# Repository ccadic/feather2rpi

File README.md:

# feather2rpi
Feather2RPIShield Adaptor
Use RPI shield / RPI display with a feather board

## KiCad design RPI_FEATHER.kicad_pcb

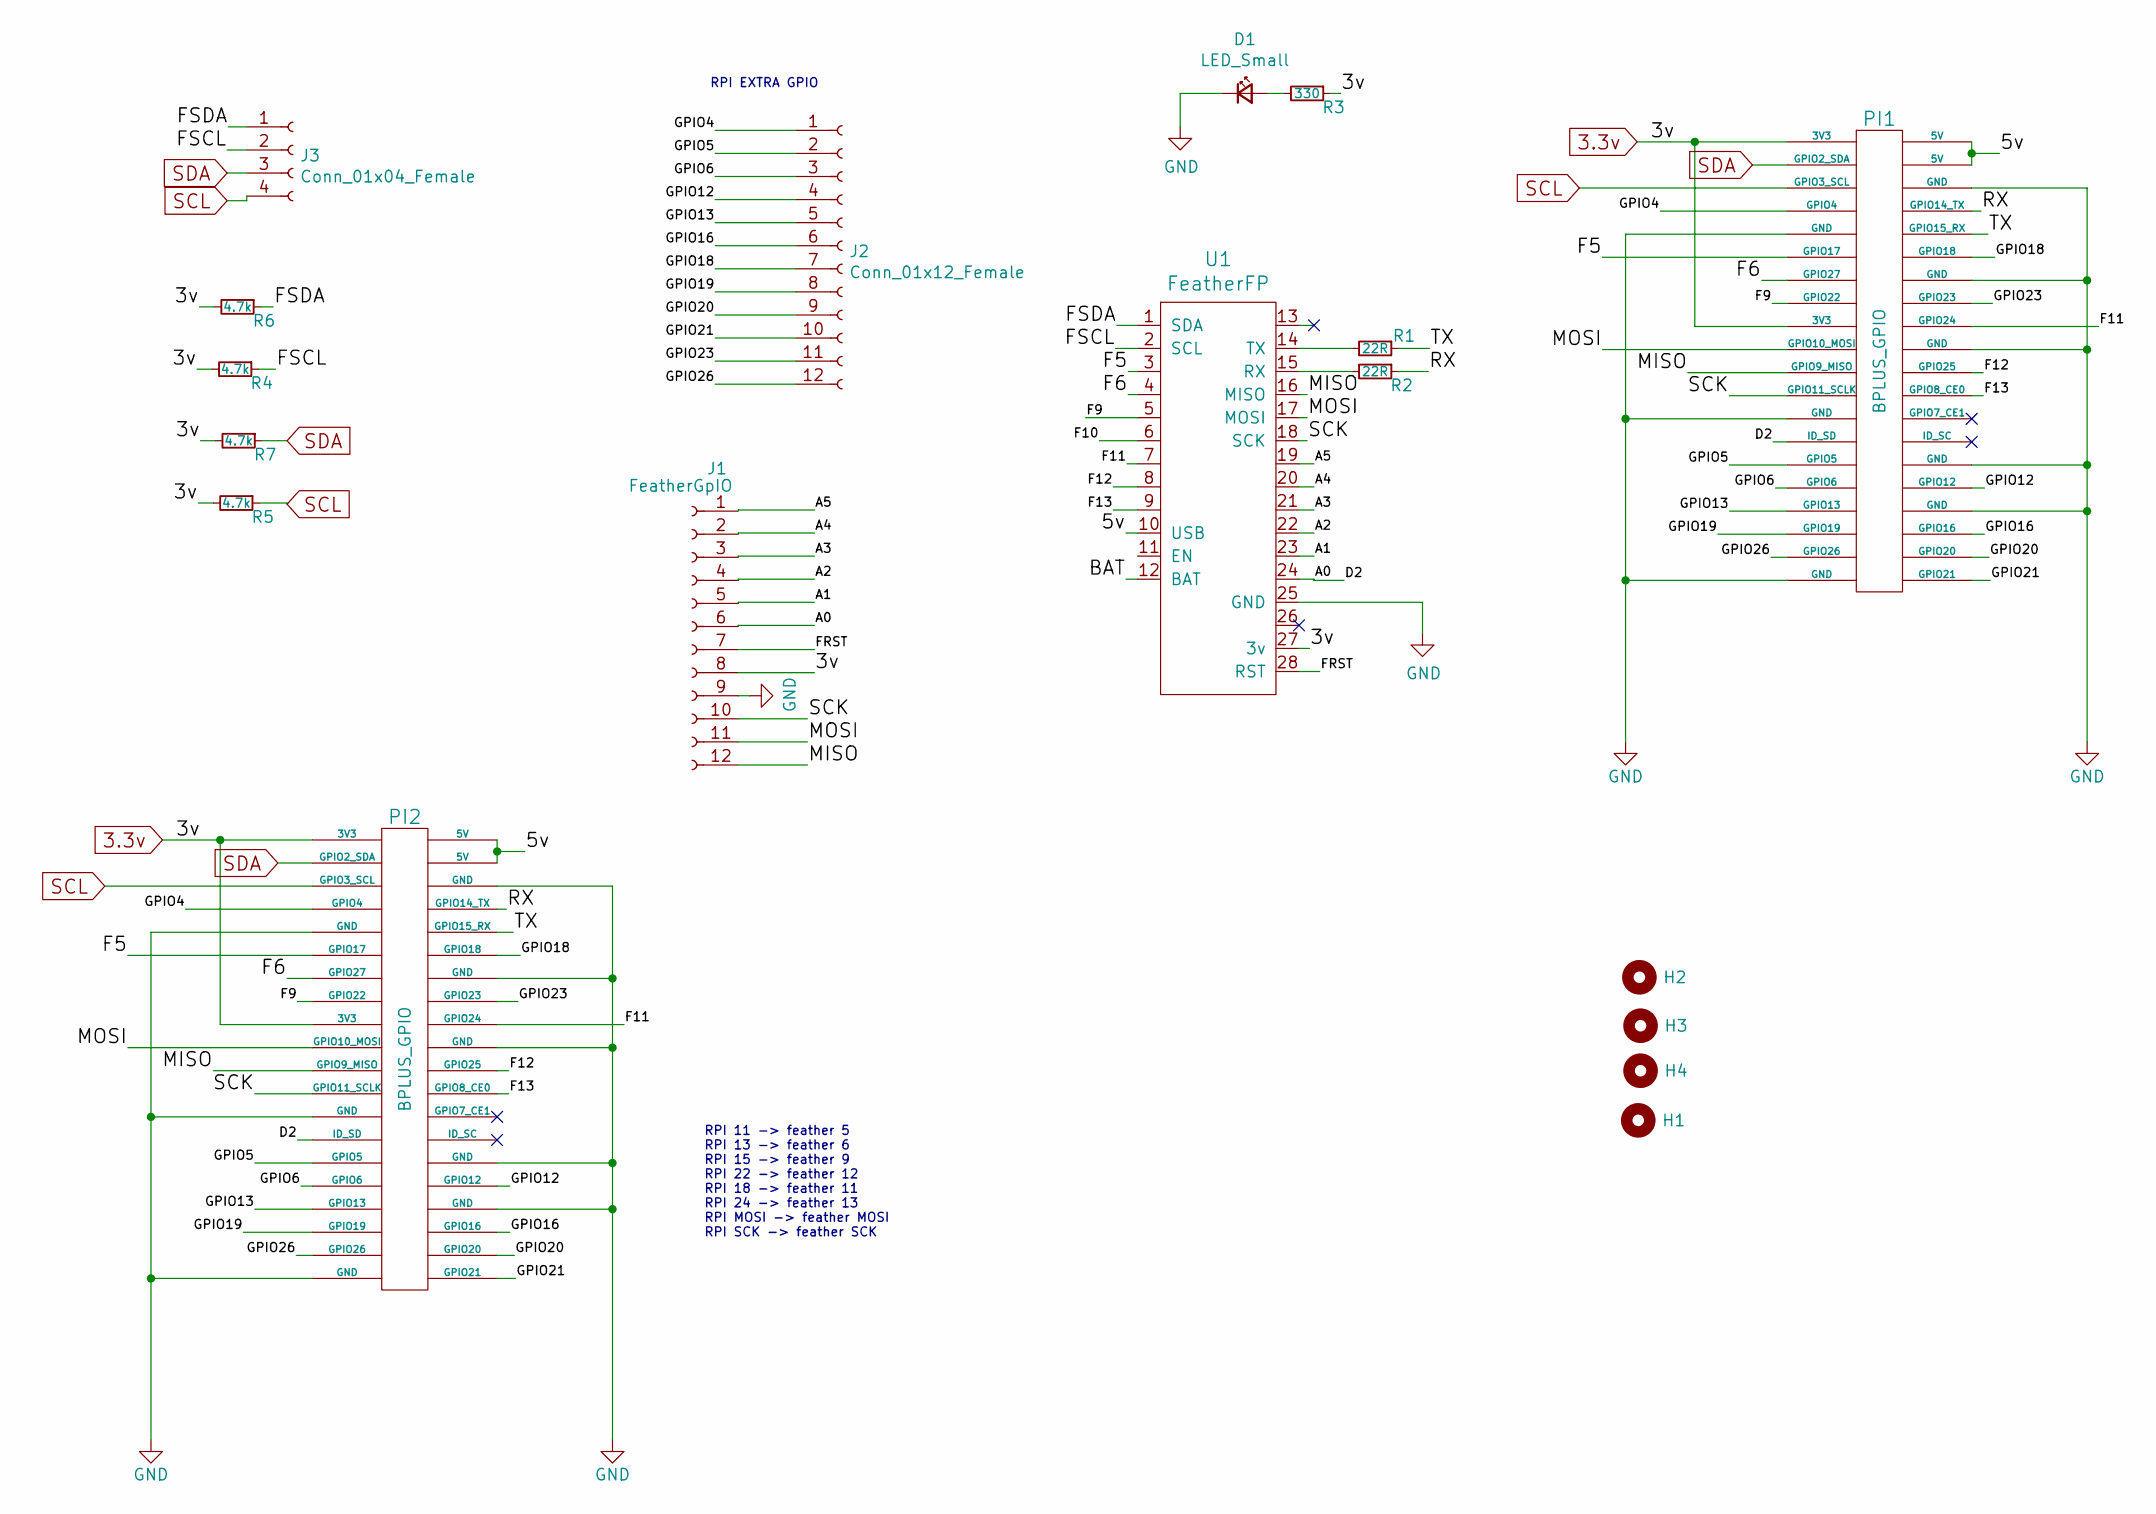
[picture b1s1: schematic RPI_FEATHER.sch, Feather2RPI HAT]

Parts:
D1: LED_Small; LED_0805_2012Metric_Pad1.15x1.40mm_HandSolder
H1, H2, H3, H4: MountingHole; MountingHole_2.2mm_M2
J1: FeatherGpIO; PinHeader_1x12_P2.54mm_Vertical
J2: Conn_01x12_Female; PinHeader_1x12_P2.54mm_Vertical
J3: Conn_01x04_Female; 4padsfree
PI1, PI2: BPLUS_GPIO; Pin_Header_Straight_2x20
R1, R2: 22R; R_0805_2012Metric_Pad1.15x1.40mm_HandSolder
R3: 330; R_0805_2012Metric_Pad1.15x1.40mm_HandSolder
R4, R5, R6, R7: 4.7k; R_0805_2012Metric_Pad1.15x1.40mm_HandSolder
U1: FeatherFP; PCB_FeatherWing

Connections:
3.3v: J1.8, PI1.1 (3V3), PI1.17 (3V3), PI2.1 (3V3), PI2.17 (3V3), R3.1, R4.2, R5.2, R6.2, R7.2, U1.27 (3v)
/5v: PI1.2 (5V), PI1.4 (5V), PI2.2 (5V), PI2.4 (5V), U1.10 (USB)
/A0: J1.6, PI1.27 (ID_SD), PI2.27 (ID_SD), U1.24
/A1: J1.5, U1.23
/A2: J1.4, U1.22
/A3: J1.3, U1.21
/A4: J1.2, U1.20
/A5: J1.1, U1.19
/F5: PI1.11 (GPIO17), PI2.11 (GPIO17), U1.3
/F6: PI1.13 (GPIO27), PI2.13 (GPIO27), U1.4
/F9: PI1.15 (GPIO22), PI2.15 (GPIO22), U1.5
/F11: PI1.18 (GPIO24), PI2.18 (GPIO24), U1.7
/F12: PI1.22 (GPIO25), PI2.22 (GPIO25), U1.8
/F13: PI1.24 (GPIO8_CE0), PI2.24 (GPIO8_CE0), U1.9
/FRST: J1.7, U1.28 (RST)
/FSCL: J3.2, R4.1, U1.2 (SCL)
/FSDA: J3.1, R6.1, U1.1 (SDA)
/GPIO4: J2.1, PI1.7 (GPIO4), PI2.7 (GPIO4)
/GPIO5: J2.2, PI1.29 (GPIO5), PI2.29 (GPIO5)
/GPIO6: J2.3, PI1.31 (GPIO6), PI2.31 (GPIO6)
/GPIO12: J2.4, PI1.32 (GPIO12), PI2.32 (GPIO12)
/GPIO13: J2.5, PI1.33 (GPIO13), PI2.33 (GPIO13)
/GPIO16: J2.6, PI1.36 (GPIO16), PI2.36 (GPIO16)
/GPIO18: J2.7, PI1.12 (GPIO18), PI2.12 (GPIO18)
/GPIO19: J2.8, PI1.35 (GPIO19), PI2.35 (GPIO19)
/GPIO20: J2.9, PI1.38 (GPIO20), PI2.38 (GPIO20)
/GPIO21: J2.10, PI1.40 (GPIO21), PI2.40 (GPIO21)
/GPIO23: J2.11, PI1.16 (GPIO23), PI2.16 (GPIO23)
/GPIO26: J2.12, PI1.37 (GPIO26), PI2.37 (GPIO26)
/MISO: J1.12, PI1.21 (GPIO9_MISO), PI2.21 (GPIO9_MISO), U1.16 (MISO)
/MOSI: J1.11, PI1.19 (GPIO10_MOSI), PI2.19 (GPIO10_MOSI), U1.17 (MOSI)
/RX: PI1.8 (GPIO14_TX), PI2.8 (GPIO14_TX), R2.1
/SCK: J1.10, PI1.23 (GPIO11_SCLK), PI2.23 (GPIO11_SCLK), U1.18 (SCK)
/TX: PI1.10 (GPIO15_RX), PI2.10 (GPIO15_RX), R1.1
GND: D1.1 (K), J1.9, PI1.6 (GND), PI1.9 (GND), PI1.14 (GND), PI1.20 (GND), PI1.25 (GND), PI1.30 (GND), PI1.34 (GND), PI1.39 (GND), PI2.6 (GND), PI2.9 (GND), PI2.14 (GND), PI2.20 (GND), PI2.25 (GND), PI2.30 (GND), PI2.34 (GND), PI2.39 (GND), U1.25 (GND)
unnamed: D1.2 (A), R3.2
unnamed: PI1.26 (GPIO7_CE1), PI2.26 (GPIO7_CE1)
unnamed: PI1.28 (ID_SC), PI2.28 (ID_SC)
unnamed: R1.2, U1.14 (TX)
unnamed: R2.2, U1.15 (RX)
SCL: J3.4, PI1.5 (GPIO3_SCL), PI2.5 (GPIO3_SCL), R5.1
SDA: J3.3, PI1.3 (GPIO2_SDA), PI2.3 (GPIO2_SDA), R7.1

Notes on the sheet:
RPI 11 -> feather 5 RPI 13 -> feather 6 RPI 15 -> feather 9 RPI 22 -> feather 12 RPI 18 -> feather 11 RPI 24 -> feather 13 RPI MOSI -> feather MOSI RPI SCK -> feather SCK
RPI EXTRA GPIO

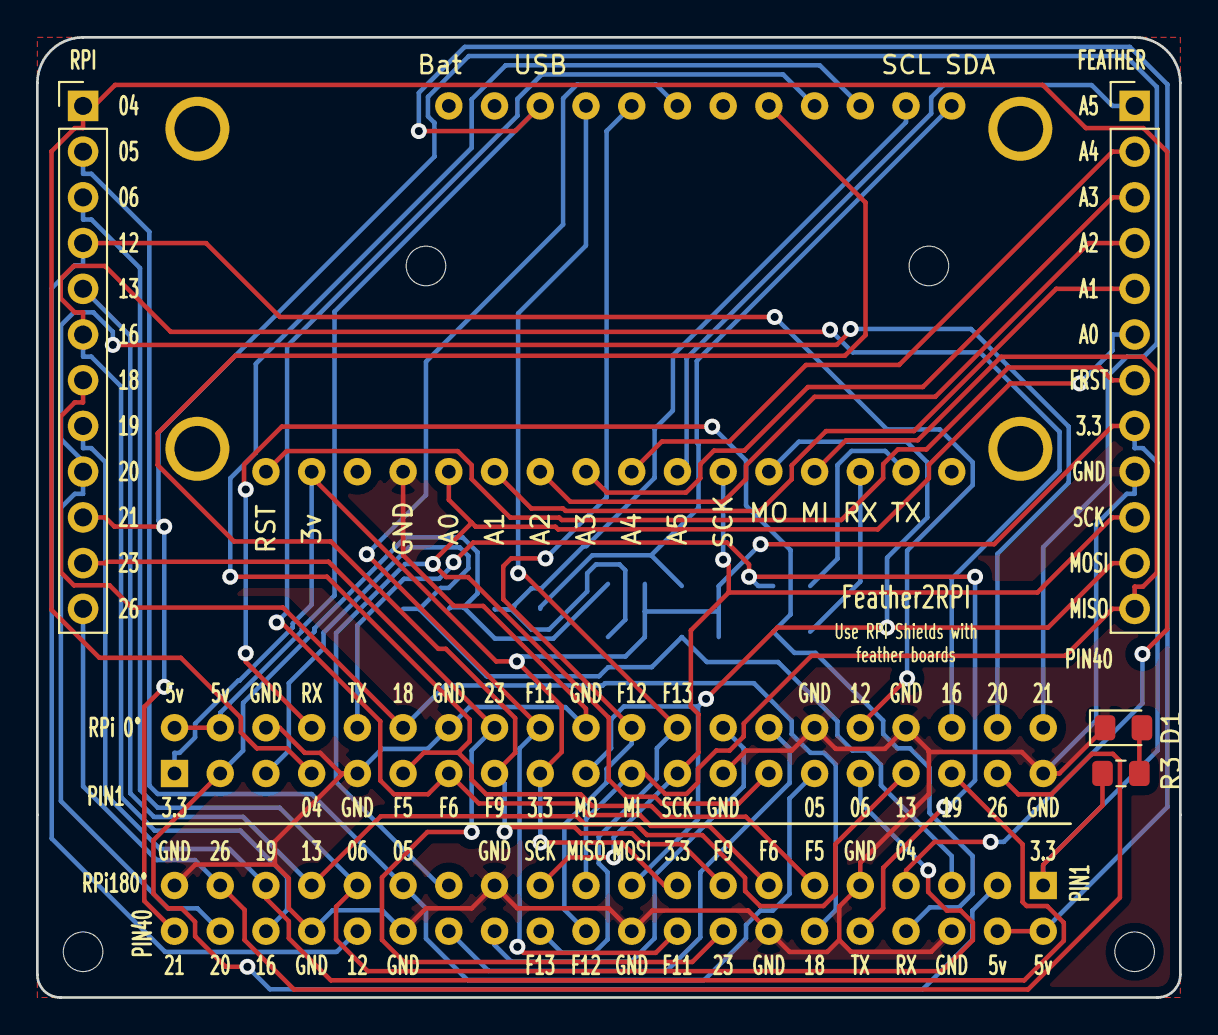
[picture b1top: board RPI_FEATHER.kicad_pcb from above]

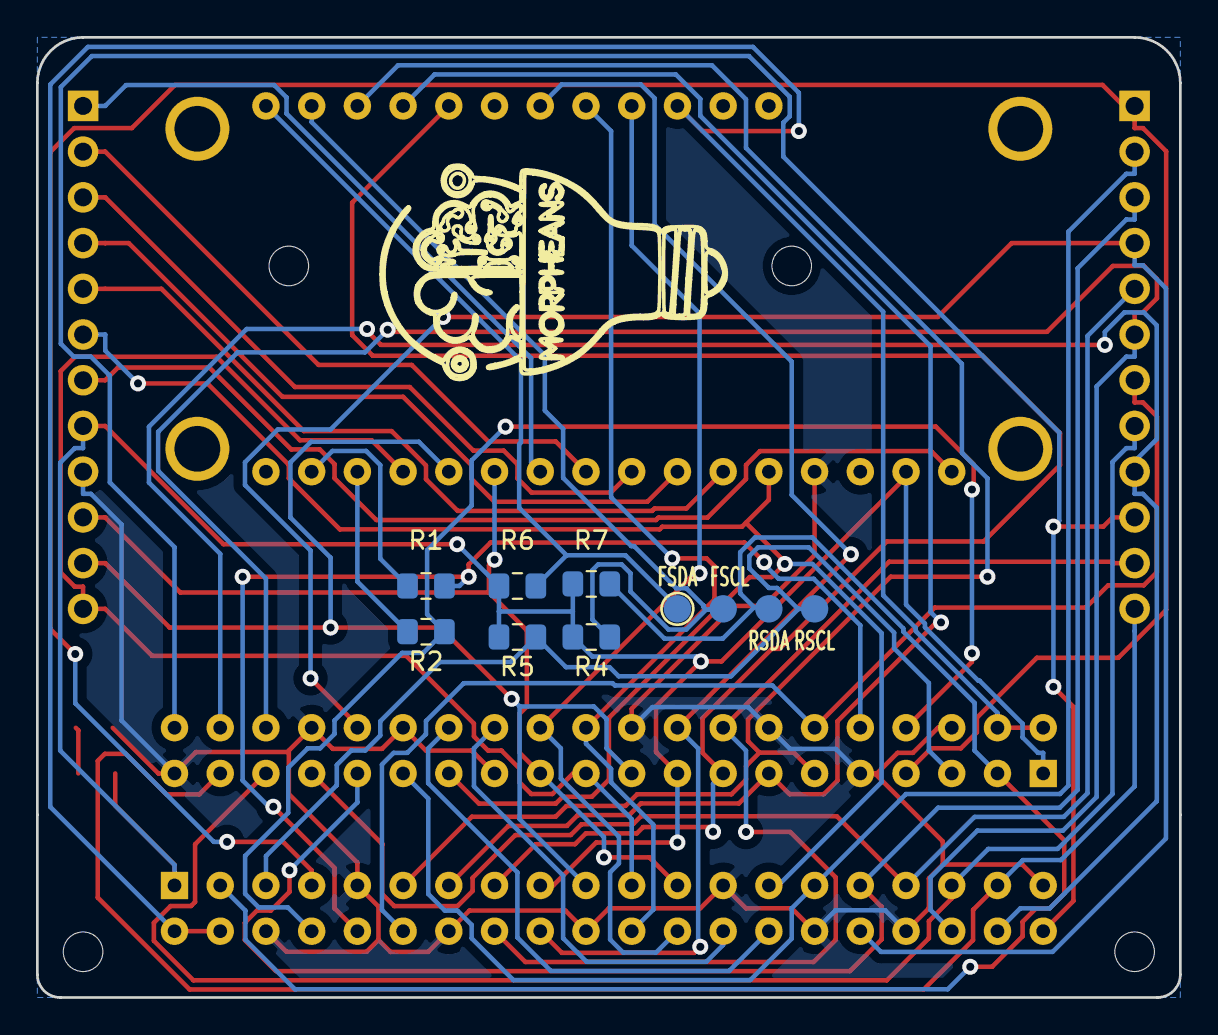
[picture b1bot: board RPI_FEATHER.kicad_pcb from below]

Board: 2 copper layers, 63.5 x 53.3 mm, 18 parts (7 on the bottom side), 42 nets.
